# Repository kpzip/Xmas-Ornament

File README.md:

# Christmas ornament
- Pcb files are in pcb folder
- code is in program folder

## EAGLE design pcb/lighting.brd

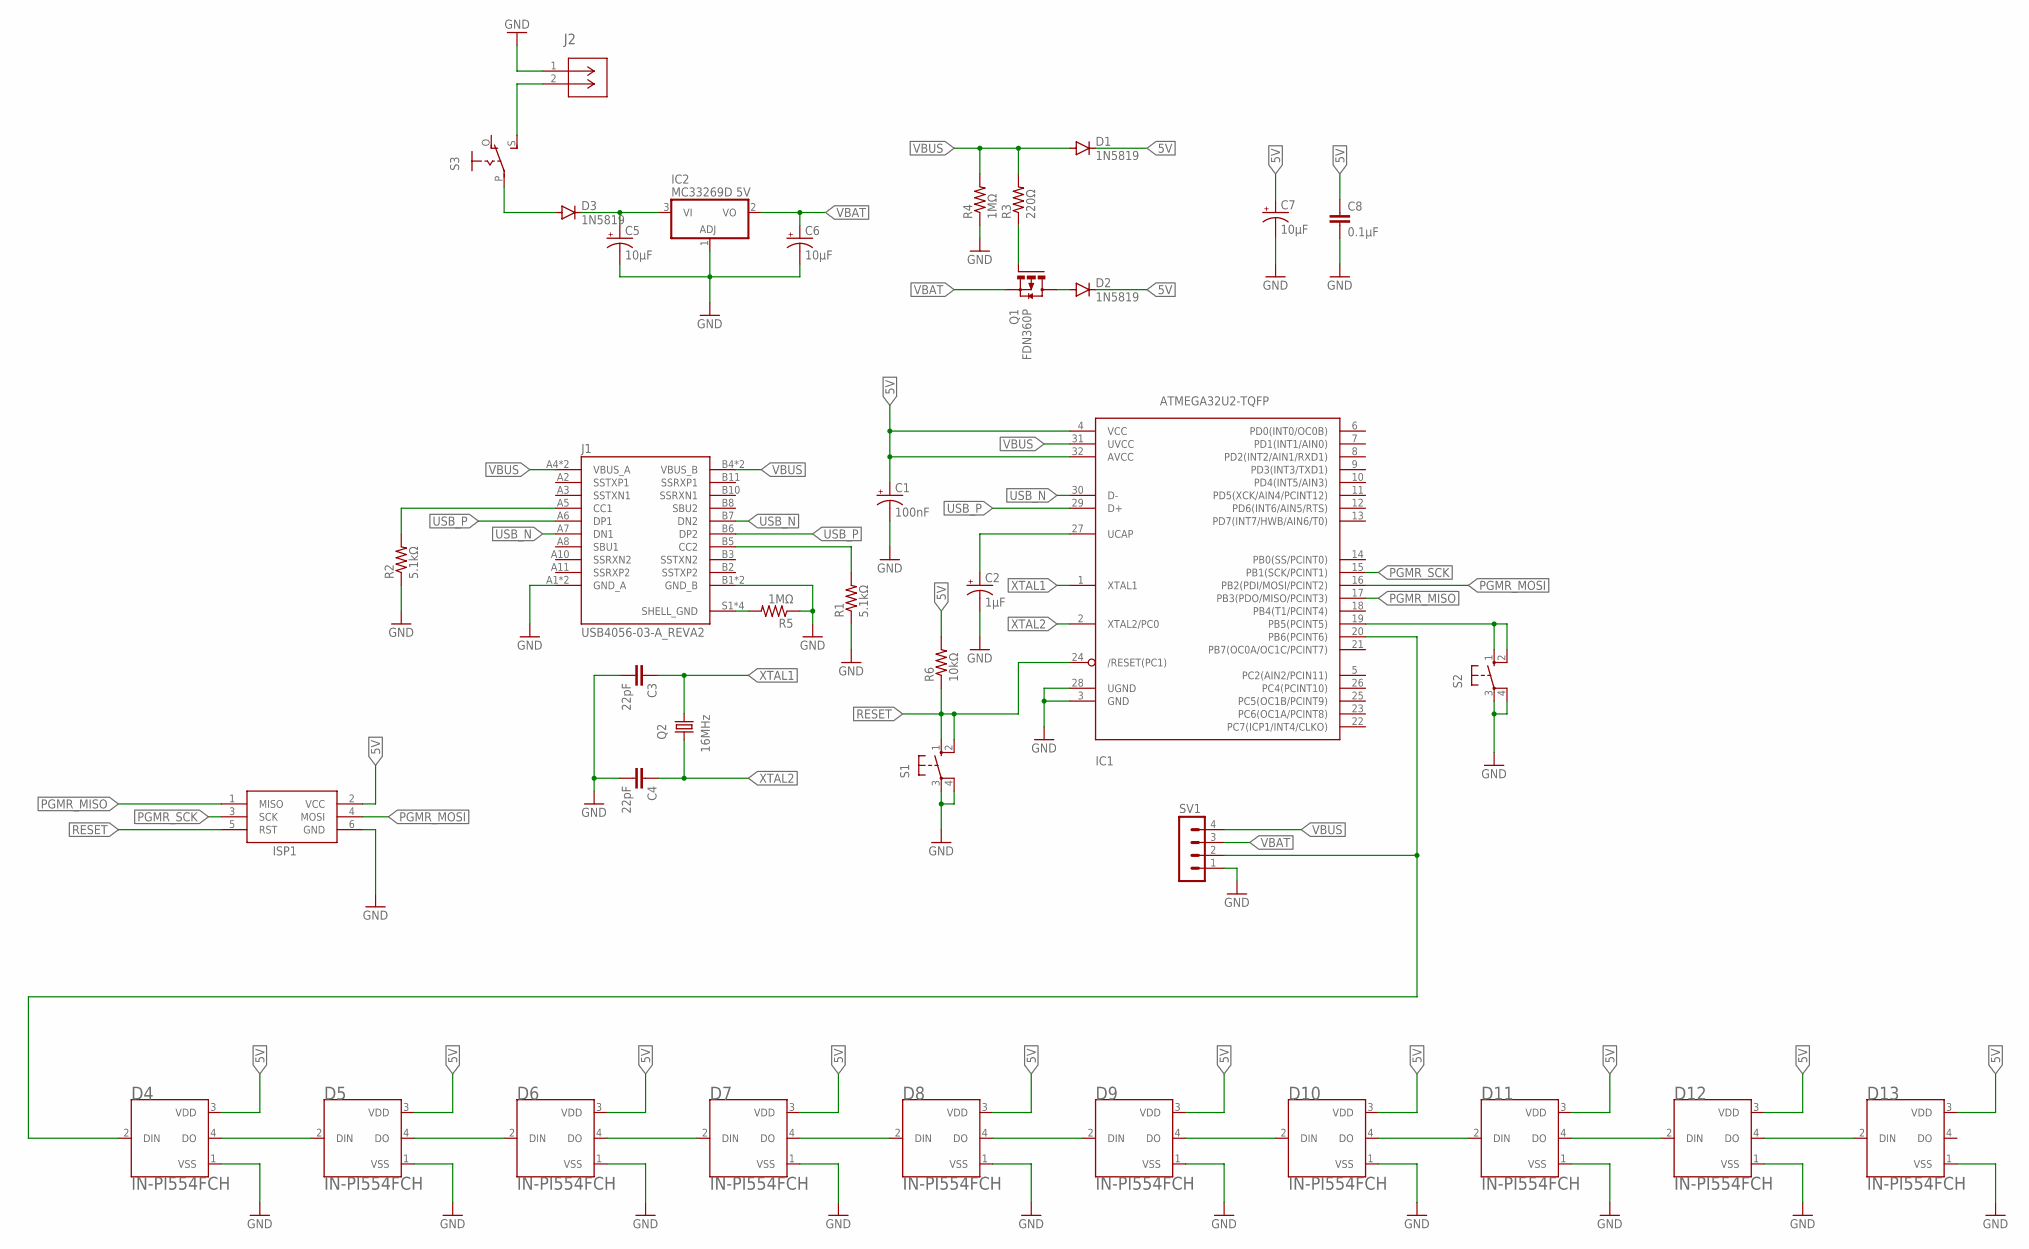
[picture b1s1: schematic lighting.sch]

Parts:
C1: 100nF; PANASONIC_B
C2: 1µF; E2-5
C3, C4: 22pF; C0402
C5, C6, C7: 10µF; PANASONIC_B
C8: 0.1µF; C0402
D1, D2, D3: 1N5819; DO15-12
D4, D5, D6, D7, D8, D9, D10, D11, D12, D13: IN-PI554FCH; LED_IN-PI554FCH
IC1: ATMEGA32U2-TQFP; TQFP32-08
IC2: MC33269D 5V; DPACK
ISP1: AVRISP-BOX
J1: USB4056-03-A_REVA2; GCT_USB4056-03-A_REVA2
J2: BH9VPC 9V; CONN_BH9VPC_MPD
Q1: FDN360P; SUPER-SOT3
Q2: 16MHz; HC49U-V
R1, R2: 5.1kΩ; 0207/10
R3: 220Ω; 0207/10
R4, R5: 1MΩ; 0207/10
R6: 10kΩ; 0207/10
S1, S2: 10-XX; B3F-10XX
S3: EG1218S; EG1218
SV1: MA04-1

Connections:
5V: C1.+, C7.+, C8.1, D1.C, D2.C, D4.3 (VDD), D5.3 (VDD), D6.3 (VDD), D7.3 (VDD), D8.3 (VDD), D9.3 (VDD), D10.3 (VDD), D11.3 (VDD), D12.3 (VDD), D13.3 (VDD), IC1.4 (VCC), IC1.32 (AVCC), ISP1.2 (VCC), R6.2
GND: C1.-, C2.-, C3.2, C4.2, C5.-, C6.-, C7.-, C8.2, D4.1 (VSS), D5.1 (VSS), D6.1 (VSS), D7.1 (VSS), D8.1 (VSS), D9.1 (VSS), D10.1 (VSS), D11.1 (VSS), D12.1 (VSS), D13.1 (VSS), IC1.3 (GND), IC1.28 (UGND), IC2.1 (ADJ), ISP1.6 (GND), J1.A1 (GND_A), J1.A12 (GND_A), J1.B1 (GND_B), J1.B12 (GND_B), J2.1, R1.1, R2.1, R4.1, R5.1, S1.3, S1.4 (P1), S2.3, S2.4 (P1), SV1.1
unnamed: J1.A5 (CC1), R2.2
unnamed: D2.A, Q1.3 (D)
unnamed: J1.B5 (CC2), R1.2
unnamed: Q1.1 (G), R3.1
unnamed: J2.2, S3.S
unnamed: C5.+, D3.C, IC2.3 (VI)
unnamed: D4.4 (DO), D5.2 (DIN)
unnamed: D5.4 (DO), D6.2 (DIN)
unnamed: D6.4 (DO), D7.2 (DIN)
unnamed: D7.4 (DO), D8.2 (DIN)
unnamed: D8.4 (DO), D9.2 (DIN)
unnamed: D9.4 (DO), D10.2 (DIN)
unnamed: D10.4 (DO), D11.2 (DIN)
unnamed: J1.S1 (SHELL_GND), J1.S2 (SHELL_GND), J1.S3 (SHELL_GND), J1.S4 (SHELL_GND), R5.2
unnamed: D4.2 (DIN), IC1.20 (PB6(PCINT6)), SV1.2
unnamed: C2.+, IC1.27 (UCAP)
unnamed: D3.A, S3.P
unnamed: IC1.19 (PB5(PCINT5)), S2.1 (S), S2.2 (S1)
unnamed: D11.4 (DO), D12.2 (DIN)
unnamed: D12.4 (DO), D13.2 (DIN)
PGMR_MISO: IC1.17 (PB3(PDO/MISO/PCINT3)), ISP1.1 (MISO)
PGMR_MOSI: IC1.16 (PB2(PDI/MOSI/PCINT2)), ISP1.4 (MOSI)
PGMR_SCK: IC1.15 (PB1(SCK/PCINT1)), ISP1.3 (SCK)
RESET: IC1.24 (/RESET(PC1)), ISP1.5 (RST), R6.1, S1.1 (S), S1.2 (S1)
USB_N: IC1.30 (D-), J1.A7 (DN1), J1.B7 (DN2)
USB_P: IC1.29 (D+), J1.A6 (DP1), J1.B6 (DP2)
VBAT: C6.+, IC2.2 (VO), Q1.2 (S), SV1.3
VBUS: D1.A, IC1.31 (UVCC), J1.A4 (VBUS_A), J1.A9 (VBUS_A), J1.B4 (VBUS_B), J1.B9 (VBUS_B), R3.2, R4.2, SV1.4
XTAL1: C3.1, IC1.1 (XTAL1), Q2.2
XTAL2: C4.1, IC1.2 (XTAL2/PC0), Q2.1

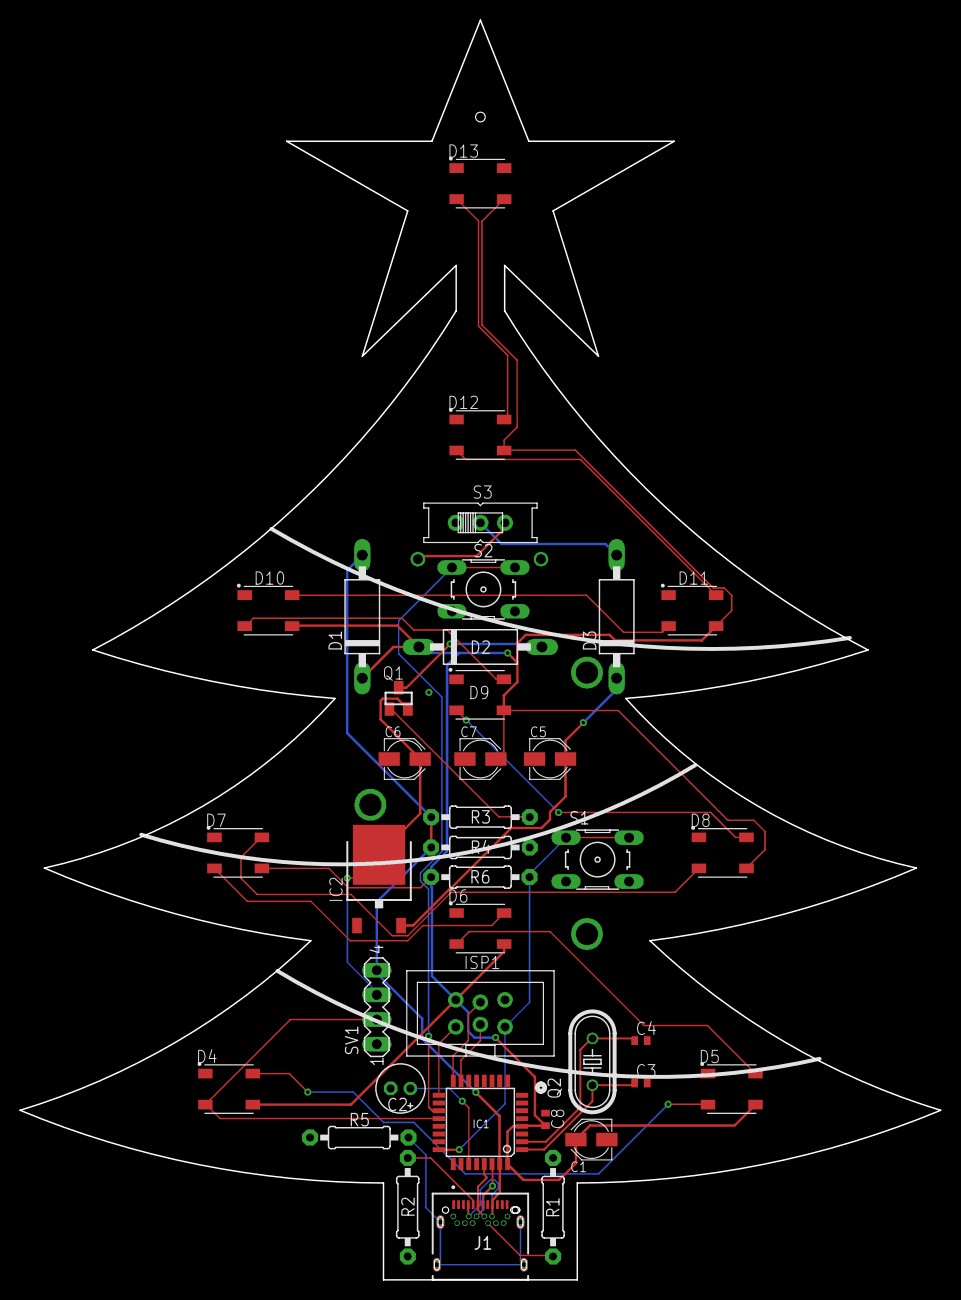
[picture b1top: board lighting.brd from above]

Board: 2 copper layers, 95.0 x 130.0 mm, 38 parts (1 on the bottom side), 32 nets.

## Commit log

2024-11-22 initialize project
2024-11-22 work
2024-12-08 progress
2024-12-09 pcb files
2024-12-09 asm it up
2024-12-10 ez pz lmn sqz
2024-12-10 housekeeping
2024-12-10 obliterate .bak files
2024-12-10 script for programming
2024-12-10 adjust timing
2024-12-10 multiple effects
2024-12-12 effects
2024-12-16 add color

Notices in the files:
parts and their libraries:
COPYRIGHT: Copyright (C) 2024 Ultra Librarian. All rights reserved.
